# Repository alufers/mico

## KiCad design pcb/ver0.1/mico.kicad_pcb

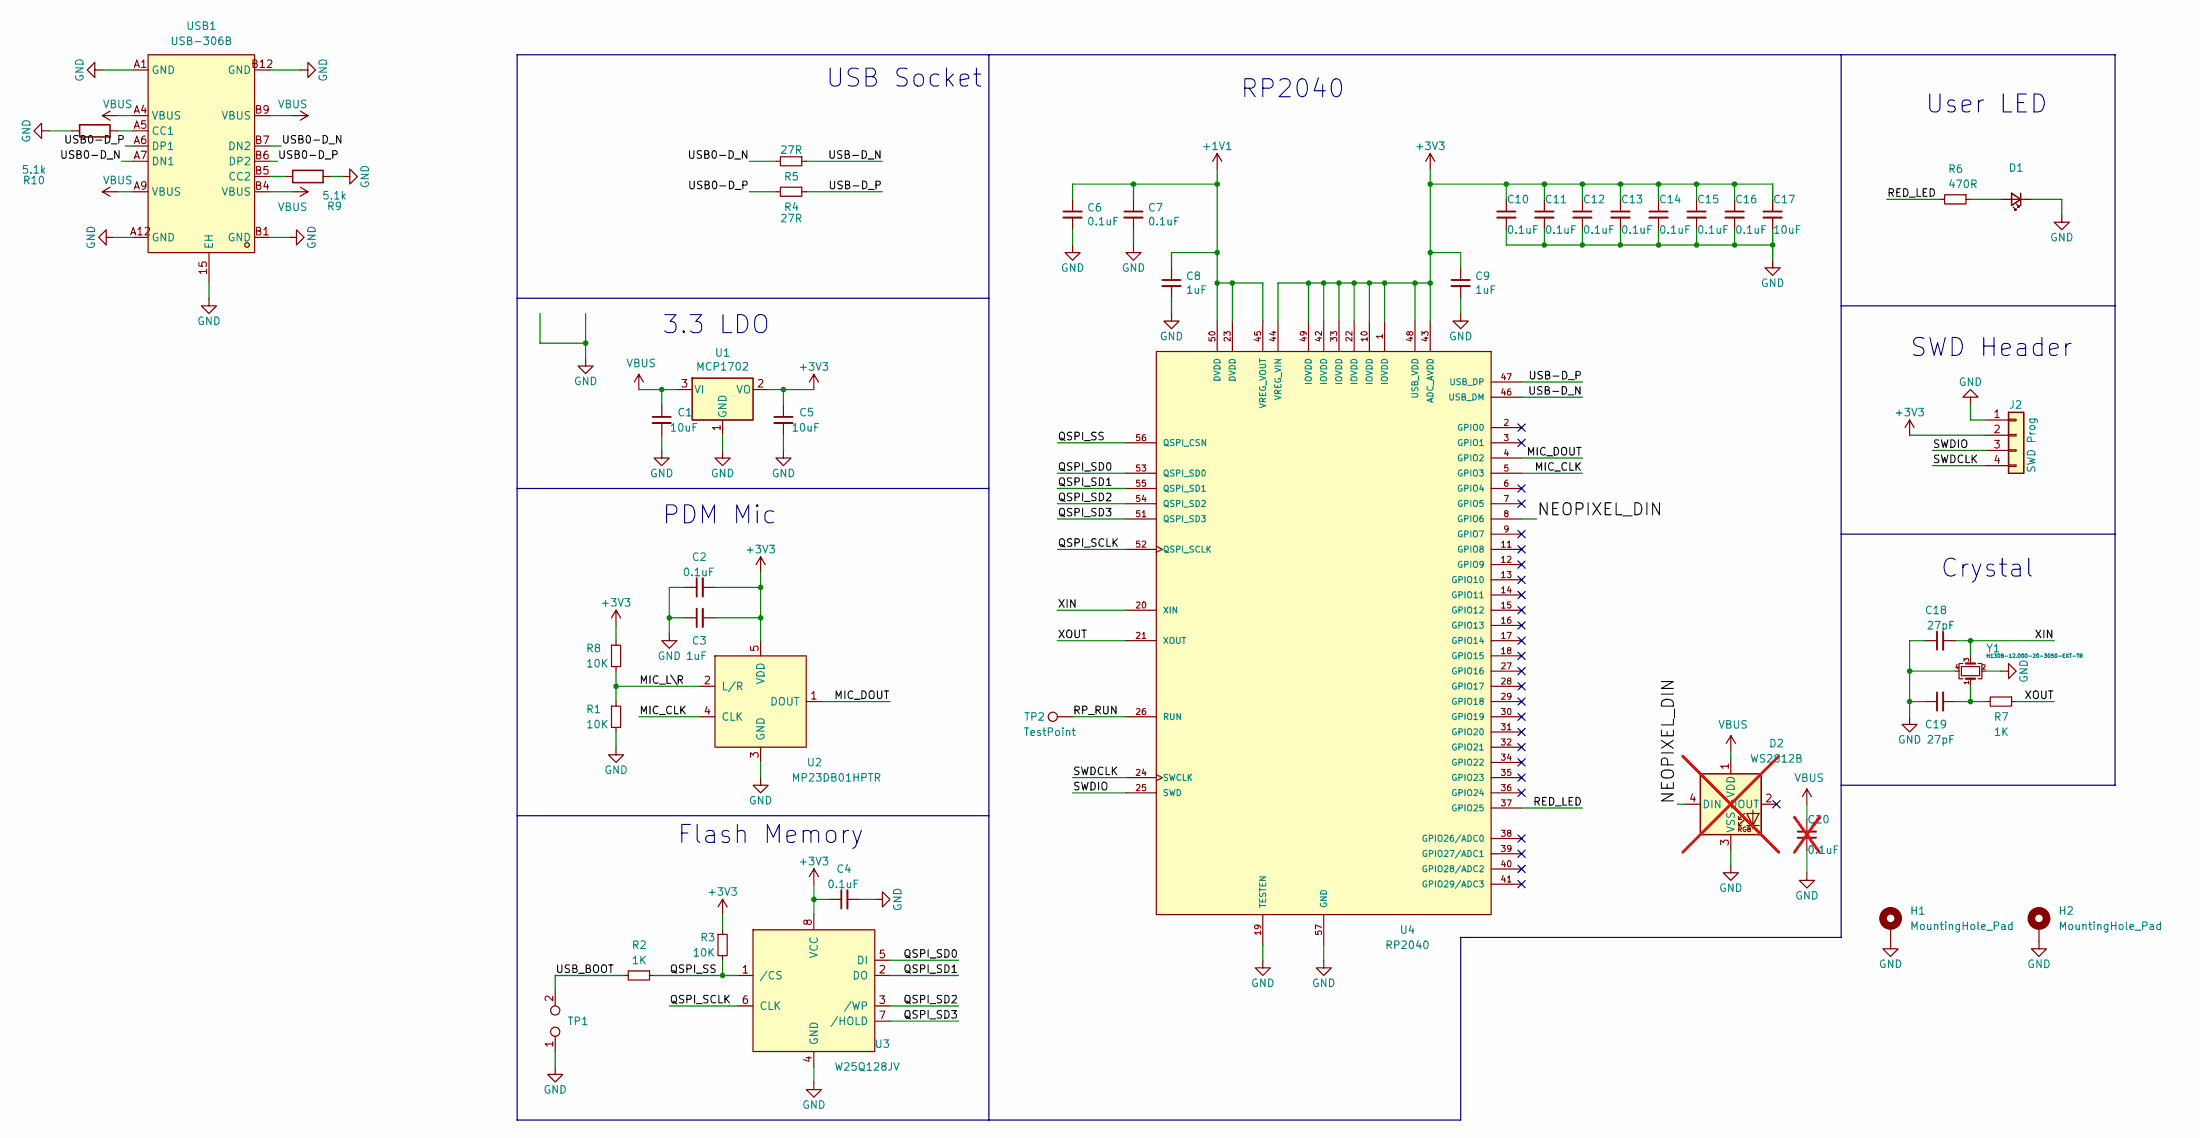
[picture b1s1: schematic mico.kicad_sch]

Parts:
C1, C5, C17: 10uF; C_0402_1005Metric
C2, C4, C6, C7, C10, C11, C12, C13, C14, C15, C16: 0.1uF; C_0402_1005Metric
C3, C8, C9: 1uF; C_0402_1005Metric
C18, C19: 27pF; C_0402_1005Metric
C20: 0.1uF; C_0402_1005Metric; not fitted
D1: LED_0603_1608Metric
D2: WS2812B; LED_WS2812B_PLCC4_5.0x5.0mm_P3.2mm; not fitted
H1, H2: MountingHole_Pad; MountingHole_3.2mm_M3_Pad
J2: SWD Prog; SMD_1x04_P1.27mm
R1, R3, R8: 10K; R_0402_1005Metric
R2, R7: 1K; R_0402_1005Metric
R4, R5: 27R; R_0402_1005Metric
R6: 470R; R_0402_1005Metric
R9, R10: 5.1k; R_0402_1005Metric
TP1: TestPoint_2Pole; SMD_1x02_P1.27mm
TP2: TestPoint; SMD_1x01_P1.27mm
U1: MCP1702; SOT-23
U2: MP23DB01HPTR; MIC_SPH0641LU4H-1
U3: W25Q128JV; SOIC-8_5.275x5.275mm_P1.27mm
U4: RP2040; QFN40P700X700X90-57N; PARTREV 1.6.1
USB1: USB-306B; USB-TYPE-C-TH_USB-306B; LCSC Part C309343
Y1: H130B-12.000-20-3050-EXT-TR; Crystal_SMD_3225-4Pin_3.2x2.5mm; JLC C5203634

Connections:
+1V1: C6.1, C7.1, C8.1, U4.23 (DVDD), U4.45 (VREG_VOUT), U4.50 (DVDD)
+3V3: C2.2, C3.2, C4.1, C5.1, C9.1, C10.1, C11.1, C12.1, C13.1, C14.1, C15.1, C16.1, C17.1, J2.2, R3.1, R8.1, U1.2 (VO), U2.5 (VDD), U3.8 (VCC), U4.1 (IOVDD), U4.10 (IOVDD), U4.22 (IOVDD), U4.33 (IOVDD), U4.42 (IOVDD), U4.43 (ADC_AVDD), U4.44 (VREG_VIN), U4.48 (USB_VDD), U4.49 (IOVDD)
/MIC_CLK: U2.4 (CLK), U4.5 (GPIO3)
/MIC_DOUT: U2.1 (DOUT), U4.4 (GPIO2)
/MIC_L\R: R1.1, R8.2, U2.2 (L/R)
/NEOPIXEL_DIN: D2.4 (DIN), U4.8 (GPIO6)
/QSPI_SCLK: U3.6 (CLK), U4.52 (QSPI_SCLK)
/QSPI_SD0: U3.5 (DI), U4.53 (QSPI_SD0)
/QSPI_SD1: U3.2 (DO), U4.55 (QSPI_SD1)
/QSPI_SD2: U3.3 (/WP), U4.54 (QSPI_SD2)
/QSPI_SD3: U3.7 (/HOLD), U4.51 (QSPI_SD3)
/QSPI_SS: R2.1, R3.2, U3.1 (/CS), U4.56 (QSPI_CSN)
/RED_LED: R6.2, U4.37 (GPIO25)
/RP_RUN: TP2.1, U4.26 (RUN)
/SWDCLK: J2.4, U4.24 (SWCLK)
/SWDIO: J2.3, U4.25 (SWD)
/USB0-D_N: R5.2, USB1.A7 (DN1), USB1.B7 (DN2)
/USB0-D_P: R4.2, USB1.A6 (DP1), USB1.B6 (DP2)
/USB-D_N: R5.1, U4.46 (USB_DM)
/USB-D_P: R4.1, U4.47 (USB_DP)
/USB_BOOT: R2.2, TP1.2
/XIN: C18.2, U4.20 (XIN), Y1.3
/XOUT: R7.1, U4.21 (XOUT)
GND: C1.2, C2.1, C3.1, C4.2, C5.2, C6.2, C7.2, C8.2, C9.2, C10.2, C11.2, C12.2, C13.2, C14.2, C15.2, C16.2, C17.2, C18.1, C19.1, C20.2, D1.1 (K), D2.3 (VSS), H1.1, H2.1, J2.1, R1.2, R9.2, R10.1, TP1.1, U1.1 (GND), U2.3 (GND), U3.4 (GND), U4.19 (TESTEN), U4.57 (GND), USB1.15 (EH), USB1.A1 (GND), USB1.A12 (GND), USB1.B1 (GND), USB1.B12 (GND), Y1.2, Y1.4
unnamed: C19.2, R7.2, Y1.1
unnamed: D1.2 (A), R6.1
unnamed: R10.2, USB1.A5 (CC1)
unnamed: R9.1, USB1.B5 (CC2)
VBUS: C1.1, C20.1, D2.1 (VDD), U1.3 (VI), USB1.A4 (VBUS), USB1.A9 (VBUS), USB1.B4 (VBUS), USB1.B9 (VBUS)

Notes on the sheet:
3.3 LDO
USB Socket
PDM Mic
Flash Memory
RP2040
Crystal
SWD Header
User LED

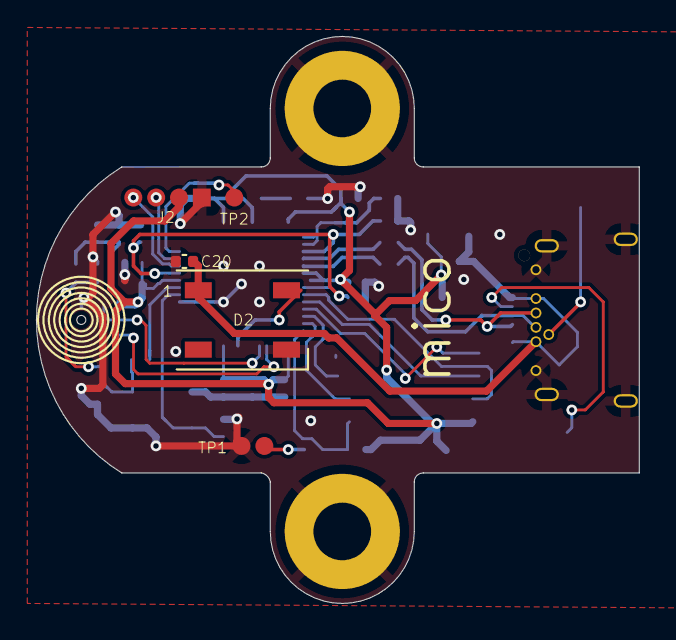
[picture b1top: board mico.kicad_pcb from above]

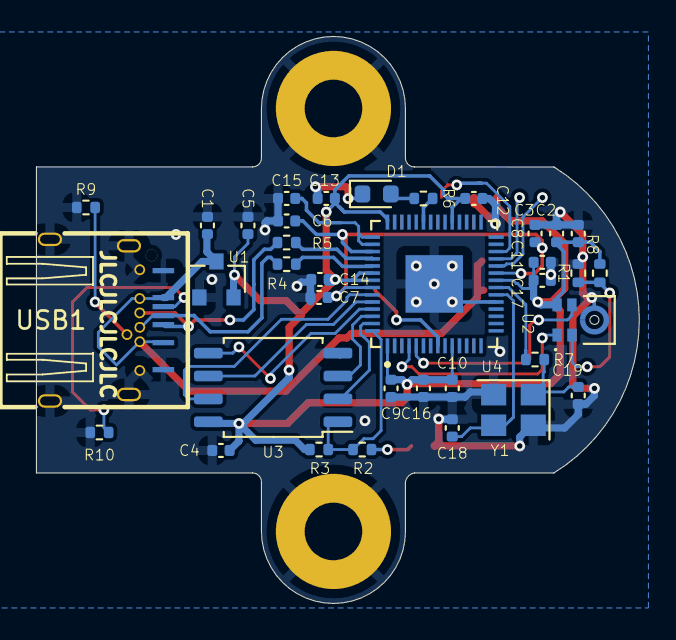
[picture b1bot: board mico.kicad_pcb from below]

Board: 2 copper layers, 33.5 x 31.5 mm, 43 parts (36 on the bottom side), 29 nets.

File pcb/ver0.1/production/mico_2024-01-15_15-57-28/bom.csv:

Designator,Footprint,Quantity,Value,LCSC Part #
"C1, C17, C5",0402,3,10uF,
"C10, C11, C12, C13, C14, C15, C16, C2, C4, C6, C7",0402,11,0.1uF,
"C18, C19",0402,2,27pF,
"C3, C8, C9",0402,3,1uF,
D1,0402,1,APA3010SECK,
"FID1, FID2, FID3",Fiducial_0.5mm_Mask1mm,3,Fiducial,
"H1, H2",MountingHole_3.2mm_M3_Pad,2,MountingHole_Pad,
J2,SMD_1x04_P1.27mm,1,SWD Prog,
"R1, R3, R8",0402,3,10K,
"R10, R9",0402,2,5.1k,
"R2, R7",0402,2,1K,
"R4, R5",0402,2,27R,
R6,0402,1,470R,
TP1,SMD_1x02_P1.27mm,1,TestPoint_2Pole,
TP2,SMD_1x01_P1.27mm,1,TestPoint,
U1,SOT-23,1,MCP1702,
U2,MIC_SPH0641LU4H-1,1,MP23DB01HPTR,
U3,PSON50P300X200X60-9N,1,W25Q128JV,
U4,QFN40P700X700X90-57N,1,RP2040,
USB1,USB-TYPE-C-TH_USB-306B,1,USB-306B,C309343
Y1,Crystal_SMD_5032-4Pin_5.0x3.2mm,1,H130B-12.000-20-3050-EXT-TR,

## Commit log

2024-02-01 hw revision with USB-C
